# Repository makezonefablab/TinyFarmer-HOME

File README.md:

# TinyFarmer@Home
==========================

[*헝그리봇 교안 - 메이크존 사이트 바로가기*](http://makezone.co.kr/blog/2014/08/14/07hungrybot/)

소개
--------------
타이니 파머를 간단하게 사용하는 방법입니다.

ESP8266 이 AP역할을하며 그 안에 서버 모듈을 탑재하여 스마트폰에서 AP를 찾아 연결하고 앱을 켜면 바로 연동이 됩니다.

타이니파머의 가정용 버전으로 온도 및 습도 센서를 통해 재배에 필요한 다양한 정보를 얻어 올 수 있습니다.

현재 출시된 센서는 토양습도, 대기습도, 대기온도의 데이터를 측정할 수 있고 작물에 따라 적절한 온도와 습도를 설정하여 상태를 확인할 수 있습니다.

또한, 아이콘을 클릭하면 토양과 대기 상태를 캐릭터로 쉽게 확인할 수 있습니다.

준비물
--------------

제작영상
--------------

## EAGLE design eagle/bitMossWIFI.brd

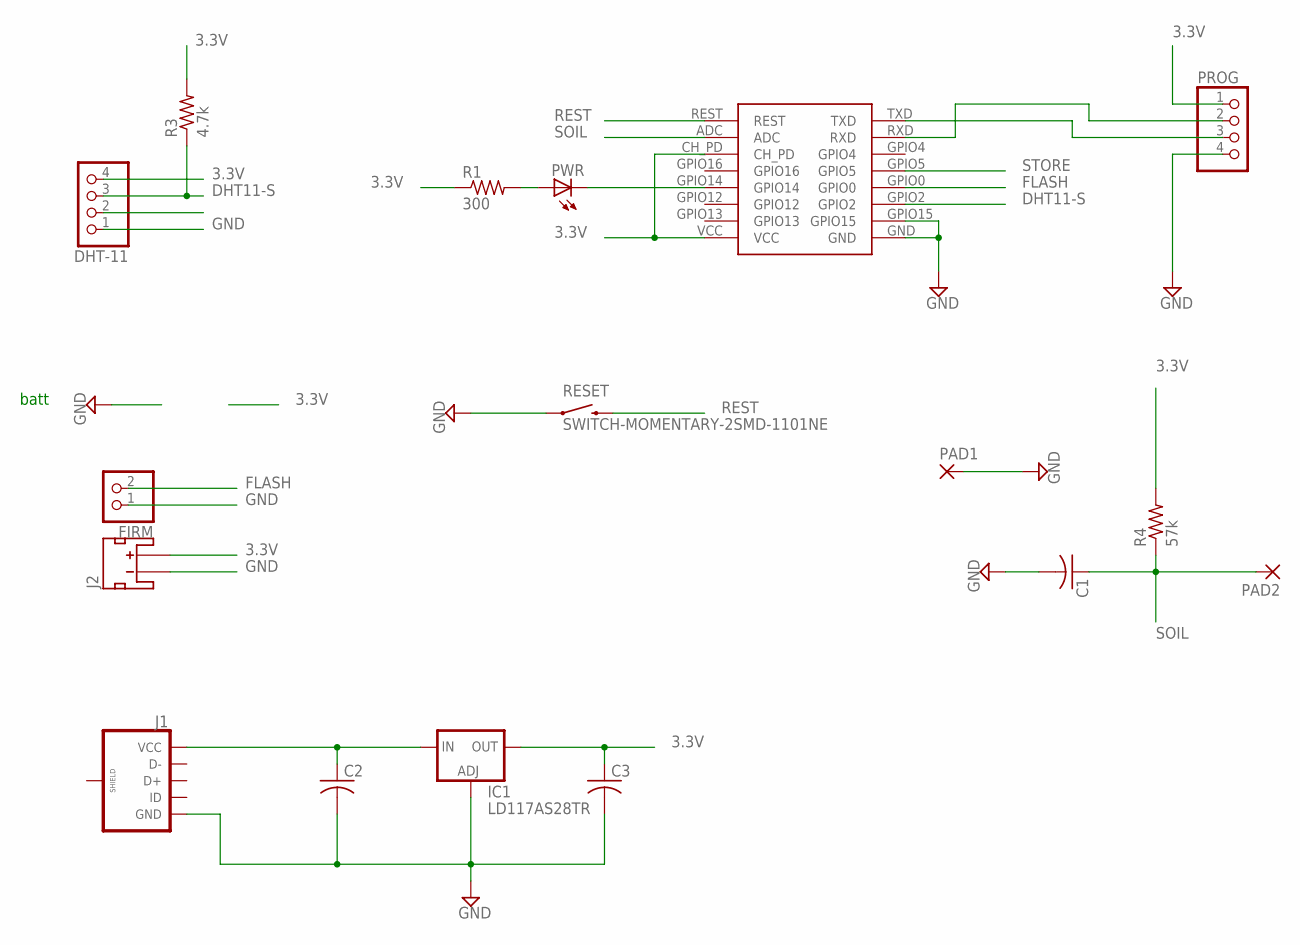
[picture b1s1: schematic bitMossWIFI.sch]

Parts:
C1: C-USC1210; C1210
C2, C3: C-USC3216; C3216
DHT-11: PINHD-1X4; 1X04
FIRM: PINHD-1X2; 1X02
IC1: LD117AS28TR; SOT223
J1: USB_MICROB_PLUGCONN-11752; USB-B-MICRO-SMD_V03
J2: JST_2MM_MALE; JST-2-SMD
PAD1, PAD2: SMD5; SMD2,54-5,08
PROG: PINHD-1X4; 1X04
PWR: LEDCHIPLED_1206; CHIPLED_1206
R1: 300; R2012
R3: 4.7k; R2012
R4: 57k; R2012
RESET: SWITCH-MOMENTARY-2SMD-1101NE; TACTILE-SWITCH-1101NE
U$2: ESP-07

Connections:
3.3V: C3.1, DHT-11.4, IC1.4 (OUT), J2.2 (+), PROG.1, R1.1, R3.2, R4.2, U$2.CH_PD, U$2.VCC
DHT11-S: DHT-11.3, R3.1, U$2.GPIO2
FLASH: FIRM.2, U$2.GPIO0
GND: C1.2, C2.2, C3.2, DHT-11.1, FIRM.1, IC1.1 (ADJ), J1.GND, J2.1 (-), PAD1.1, PROG.4, RESET.1, U$2.GND, U$2.GPIO15
unnamed: PWR.C, U$2.GPIO14
unnamed: PWR.A, R1.2
unnamed: C2.1, IC1.3 (IN), J1.VBUS (VCC)
unnamed: PROG.3, U$2.TXD
unnamed: PROG.2, U$2.RXD
REST: RESET.2, U$2.REST
SOIL: C1.1, PAD2.1, R4.1, U$2.ADC
STORE: U$2.GPIO5

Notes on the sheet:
batt

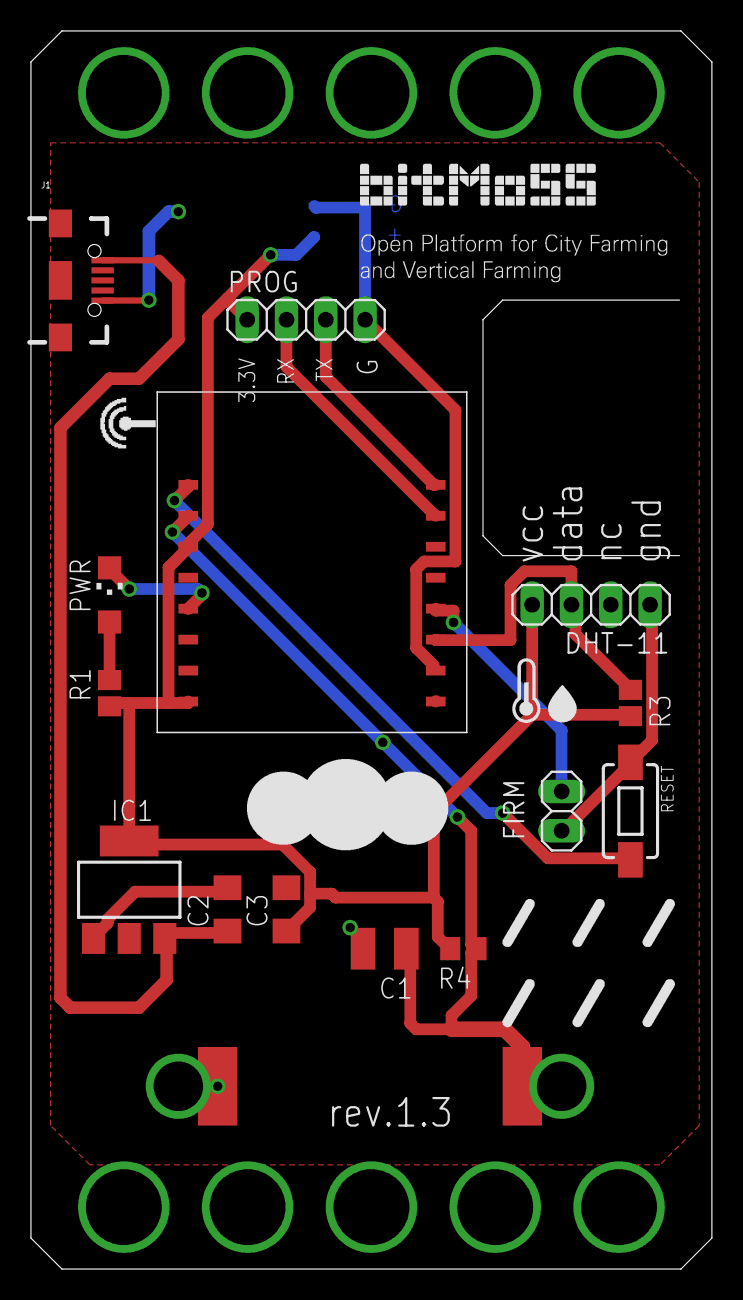
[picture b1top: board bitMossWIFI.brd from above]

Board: 2 copper layers, 44.0 x 80.0 mm, 22 parts (1 on the bottom side), 11 nets.

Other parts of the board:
U$1: BITMOSS_S_TITLE
U$3: TINYFARMER-HUMI_TEMP
U$4: TINYFARMER-RAIN1
U$5: TINYFARMER-CLOUD
U$6: CREBBOX_V_RF

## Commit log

2016-05-20 :neckbeard: Added .gitattributes & .gitignore files
2016-05-20 TinyFarmer @ Home
    pleasure
2016-05-20 TinyFarmer@Home
    TinyFarmer@Home
2016-05-20 eagle cad files
2016-05-20 arduino source
    you should do under ESP8266 board mode

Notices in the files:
parts and their libraries:
SparkFun-Connectors: Licensing: Creative Commons ShareAlike 4.0 International - https://creativecommons.org/licenses/by-sa/4.0
